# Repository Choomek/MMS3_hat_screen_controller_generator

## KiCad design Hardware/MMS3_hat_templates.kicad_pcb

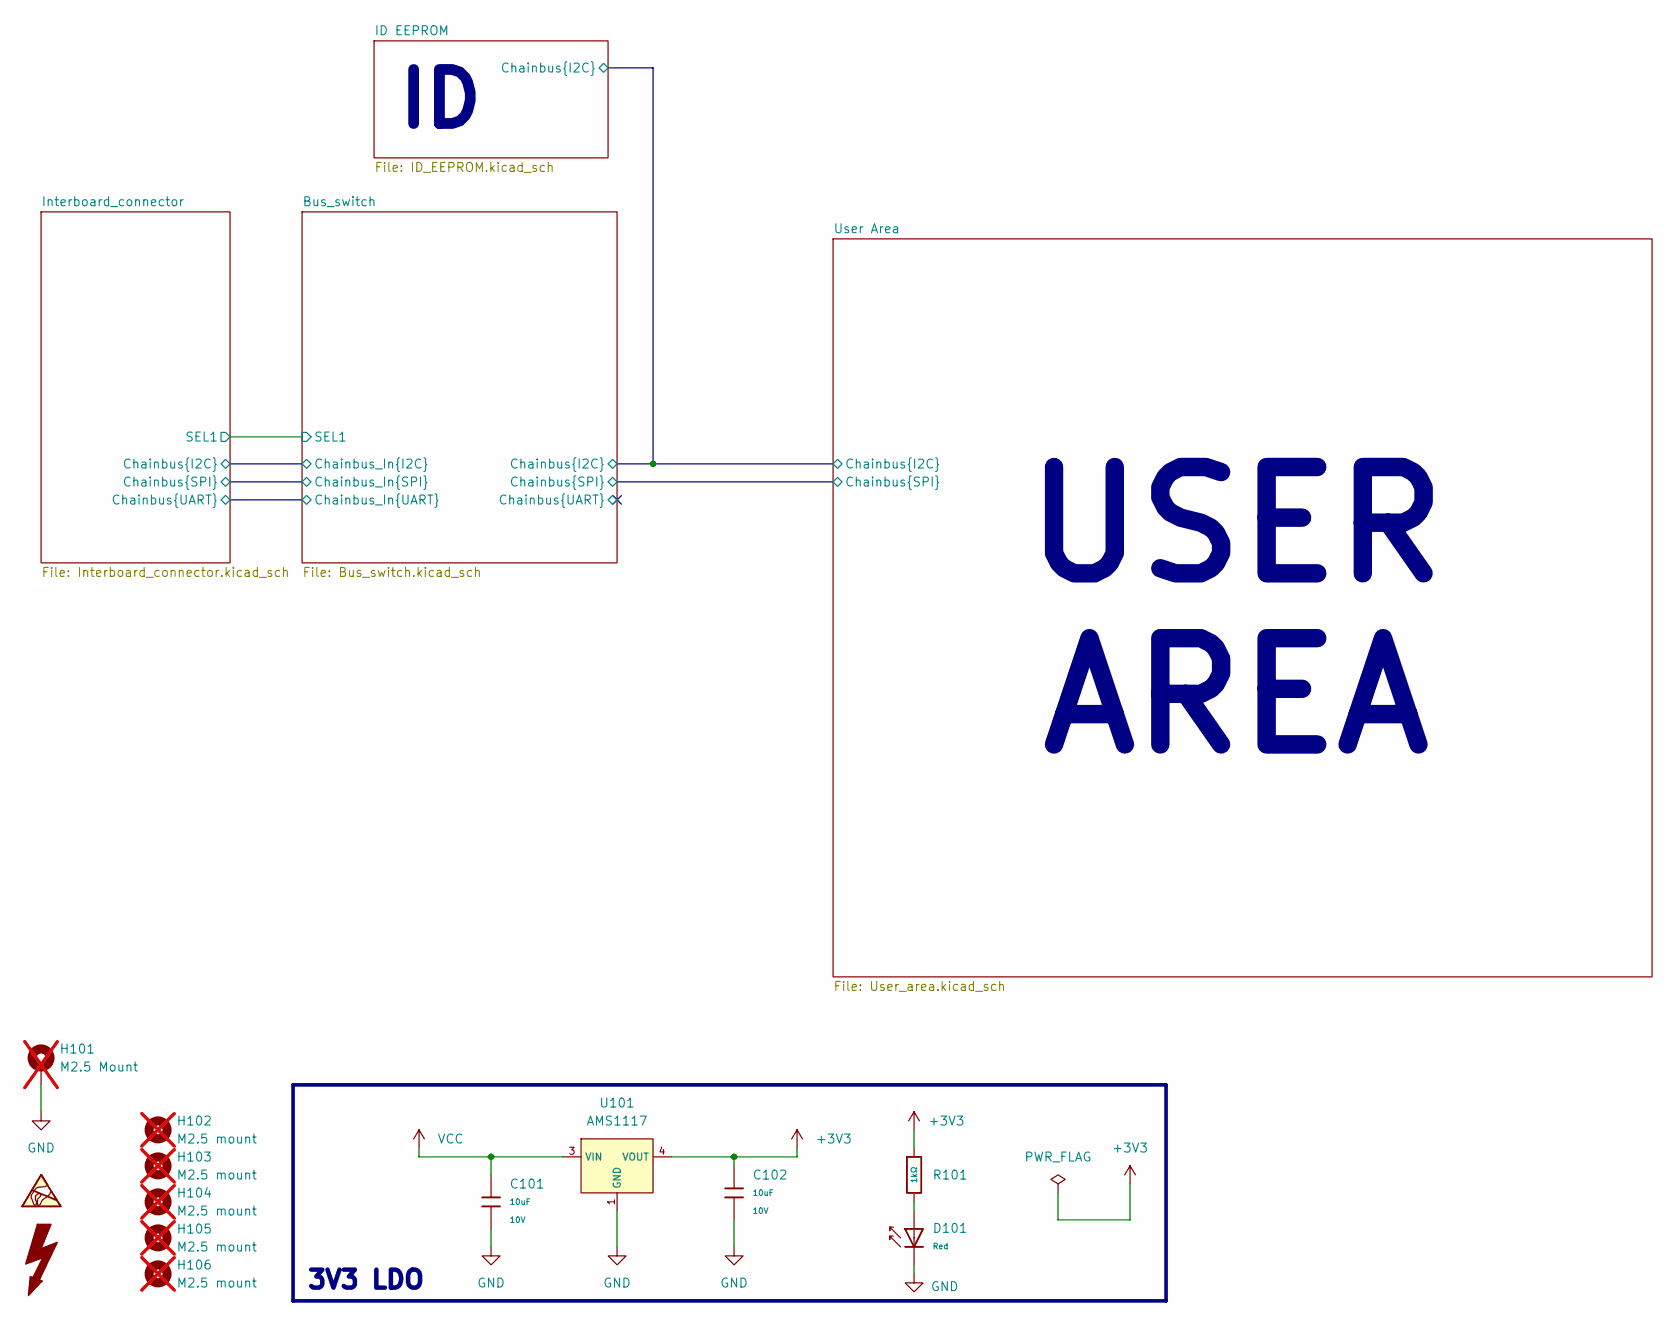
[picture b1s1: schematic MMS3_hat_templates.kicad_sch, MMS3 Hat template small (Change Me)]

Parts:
C101, C102: 10uF; C_0603; Voltage Rated 10V; Tolerance ±10%; Part CL10A106KP8NNNC; LCSC C19702
D101: Red; D_0603; Part KT-0603R; LCSC C2286
H101: M2.5 Mount; MountingHole_2.7mm_M2.5_DIN965_Pad_TopOnly; not fitted
H102, H103, H104, H105, H106: M2.5 mount; MountingHole_2.7mm_M2.5; not fitted
R101: 1kΩ; R_0603; Overload Voltage (Max) 75V; Tolerance ±1%; Part 0603WAF1001T5E; LCSC C21190
U101: AMS1117; SOT-223-3_L6.5-W3.4-P2.30-LS7.0-BR; Output Voltage 3.3V; Dropout Voltage 1.3V@(800mA); Part AMS1117-3.3; LCSC C6186

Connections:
+3V3: C102.1, R101.1, U101.2 (VOUT), U101.4 (VOUT); also elsewhere on the board
GND: C101.2, C102.2, D101.1, H101.1 (1_1), U101.1 (GND); also elsewhere on the board
unnamed: D101.2, R101.2
VCC: C101.1, U101.3 (VIN); also elsewhere on the board

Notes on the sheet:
3V3 LDO
USER AREA

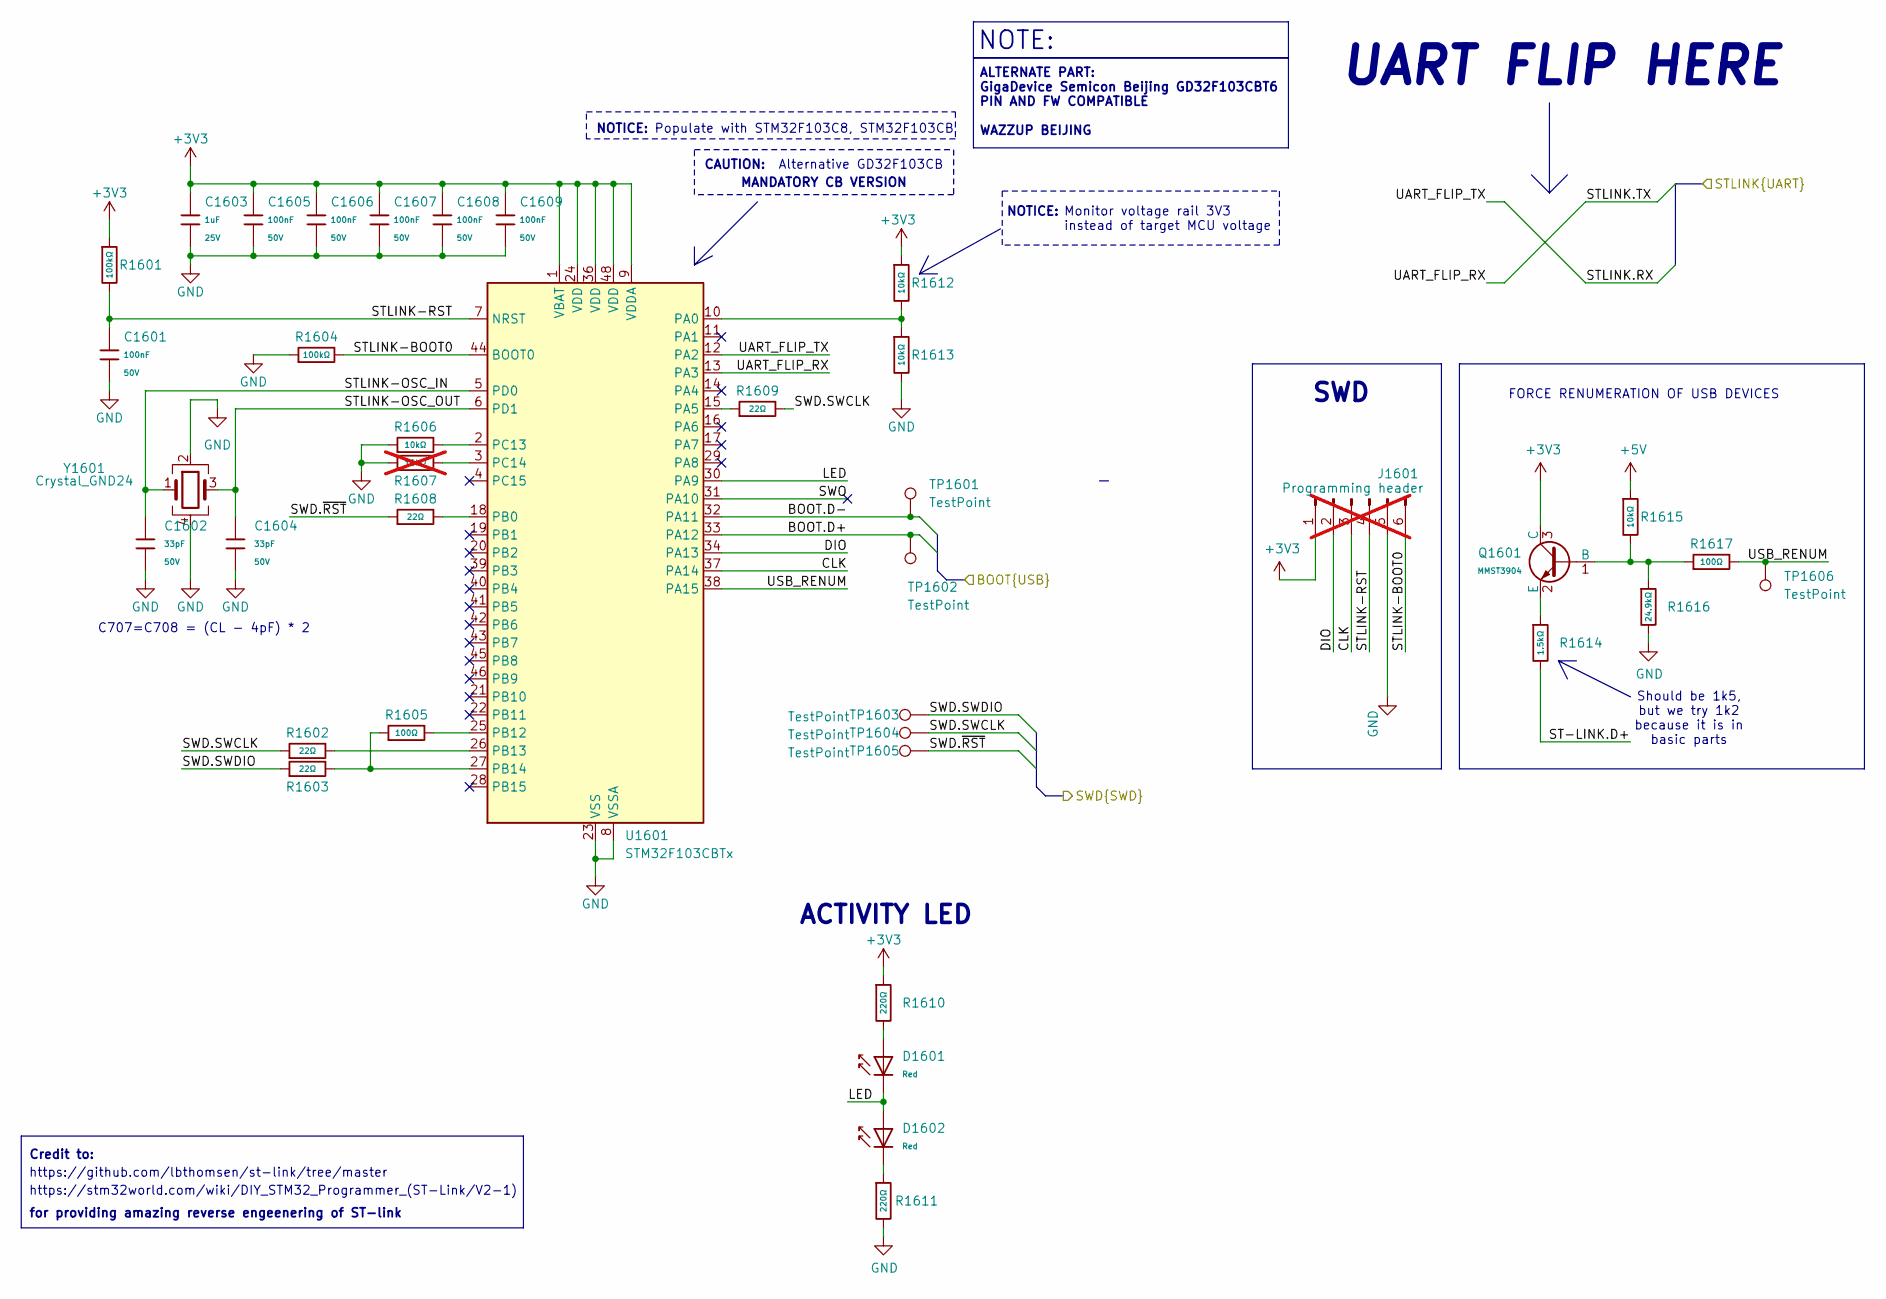
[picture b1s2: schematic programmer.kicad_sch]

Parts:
C1601, C1605, C1606, C1607, C1608, C1609: 100nF; C_0402; Voltage Rated 50V; Tolerance ±10%; Part CL05B104KB54PNC; LCSC C307331
C1602, C1604: 33pF; C_0402; Voltage Rated 50V; Tolerance ±5%; Part 0402CG330J500NT; LCSC C1562
C1603: 1uF; C_0402; Voltage Rated 25V; Tolerance ±10%; Part CL05A105KA5NQNC; LCSC C52923
D1601, D1602: Red; D_0603; Part KT-0603R; LCSC C2286
J1601: Programming header; PinHeader_1x06_P1.27mm_Vertical; not fitted
Q1601: MMST3904; SOT-23; Part MMST3904; LCSC C20526
R1601, R1604: 100kΩ; R_0402; Overload Voltage (Max) 50V; Tolerance ±1%; Part 0402WGF1003TCE; LCSC C25741
R1602, R1603, R1608, R1609: 22Ω; R_0402; Overload Voltage (Max) 50V; Tolerance ±1%; Part 0402WGF220JTCE; LCSC C25092
R1605, R1617: 100Ω; R_0402; Overload Voltage (Max) 50V; Tolerance ±1%; Part 0402WGF1000TCE; LCSC C25076
R1606, R1612, R1613, R1615: 10kΩ; R_0402; Overload Voltage (Max) 50V; Tolerance ±1%; Part 0402WGF1002TCE; LCSC C25744
R1607: 10kΩ; R_0402; Overload Voltage (Max) 50V; Tolerance ±1%; Part 0402WGF1002TCE; LCSC C25744; not fitted
R1610, R1611: 220Ω; R_0402; Overload Voltage (Max) 50V; Tolerance ±1%; Part 0402WGF2200TCE; LCSC C25091
R1614: 1.5kΩ; R_0402; Overload Voltage (Max) 50V; Tolerance ±1%; Part 0402WGF1501TCE; LCSC C25867
R1616: 24.9kΩ; R_0402; Overload Voltage (Max) 50V; Tolerance ±1%; Part 0402WGF2402TCE; LCSC C25874
TP1601, TP1602, TP1603, TP1604, TP1605, TP1606: TestPoint; TestPoint_Pad_D1.0mm
U1601: STM32F103CBTx; LQFP-48_7x7mm_P0.5mm; LCSC C8304
Y1601: Crystal_GND24; CRYSTAL-SMD_4P-L3.2-W2.5-BL; MPN 3225-8.00-20-10-10/4B; LCSC C7424755

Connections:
+3V3: C1603.1, C1605.1, C1606.1, C1607.1, C1608.1, C1609.1, J1601.1, Q1601.3 (C), R1601.1, R1610.1, R1612.1, U1601.1 (VBAT), U1601.9 (VDDA), U1601.24 (VDD), U1601.36 (VDD), U1601.48 (VDD); also elsewhere on the board
+5V: R1615.1; also elsewhere on the board
/User Area/BOOT USB/BOOT.D+: TP1602.1 (1_1), U1601.33 (PA12); also elsewhere on the board
/User Area/BOOT USB/BOOT.D-: TP1601.1 (1_1), U1601.32 (PA11); also elsewhere on the board
/User Area/MCU/PROG_SWD.SWCLK: R1602.1, R1609.2, TP1604.1 (1_1); also elsewhere on the board
/User Area/MCU/PROG_SWD.SWDIO: R1603.1, TP1603.1 (1_1); also elsewhere on the board
/User Area/MCU/PROG_SWD.~RST: R1608.1, TP1605.1 (1_1); also elsewhere on the board
/User Area/programmer/CLK: J1601.3, U1601.37 (PA14)
/User Area/programmer/DIO: J1601.2, U1601.34 (PA13)
/User Area/programmer/LED: D1601.1, D1602.2, U1601.30 (PA9)
/User Area/programmer/ST-LINK.D+: R1614.2
/User Area/programmer/STLINK-BOOT0: J1601.6, R1604.2, U1601.44 (BOOT0)
/User Area/programmer/STLINK-OSC_IN: C1602.1, U1601.5 (PD0), Y1601.1
/User Area/programmer/STLINK-OSC_OUT: C1604.1, U1601.6 (PD1), Y1601.3
/User Area/programmer/STLINK-RST: C1601.1, J1601.4, R1601.2, U1601.7 (NRST)
/User Area/programmer/STLINK.RX: U1601.12 (PA2)
/User Area/programmer/STLINK.TX: U1601.13 (PA3)
/User Area/programmer/SWO: U1601.31 (PA10)
/User Area/programmer/USB_RENUM: R1617.2, TP1606.1 (1_1), U1601.38 (PA15)
GND: C1601.2, C1602.2, C1603.2, C1604.2, C1605.2, C1606.2, C1607.2, C1608.2, C1609.2, J1601.5, R1604.1, R1606.1, R1607.1, R1611.2, R1613.2, R1616.2, U1601.8 (VSSA), U1601.23 (VSS), U1601.35 (VSS), U1601.47 (VSS), Y1601.2, Y1601.4; also elsewhere on the board
unnamed: D1601.2, R1610.2
unnamed: D1602.1, R1611.1
unnamed: Q1601.1 (B), R1615.2, R1616.1, R1617.1
unnamed: Q1601.2 (E), R1614.1
unnamed: R1612.2, R1613.1, U1601.10 (PA0)
unnamed: R1609.1, U1601.15 (PA5)
unnamed: R1608.2, U1601.18 (PB0)
unnamed: R1605.2, U1601.25 (PB12)
unnamed: R1602.2, U1601.26 (PB13)
unnamed: R1603.2, R1605.1, U1601.27 (PB14)
unnamed: R1606.2, U1601.2 (PC13)
unnamed: R1607.2, U1601.3 (PC14)

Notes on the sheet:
Alternative GD32F103CB
Monitor voltage rail 3V3 instead of target MCU voltage
SWD
for providing amazing reverse engeenering of ST-link
MANDATORY CB VERSION
NOTICE:
FORCE RENUMERATION OF USB DEVICES
UART FLIP HERE
C707=C708 = (CL - 4pF) * 2
Should be 1k5, but we try 1k2 because it is in basic parts
https://github.com/lbthomsen/st-link/tree/master
https://stm32world.com/wiki/DIY_STM32_Programmer_(ST-Link/V2-1)
ACTIVITY LED
ALTERNATE PART: GigaDevice Semicon Beijing GD32F103CBT6 PIN AND FW COMPATIBLE WAZZUP BEIJING
Populate with STM32F103C8, STM32F103CB
NOTE:
Credit to:
CAUTION:

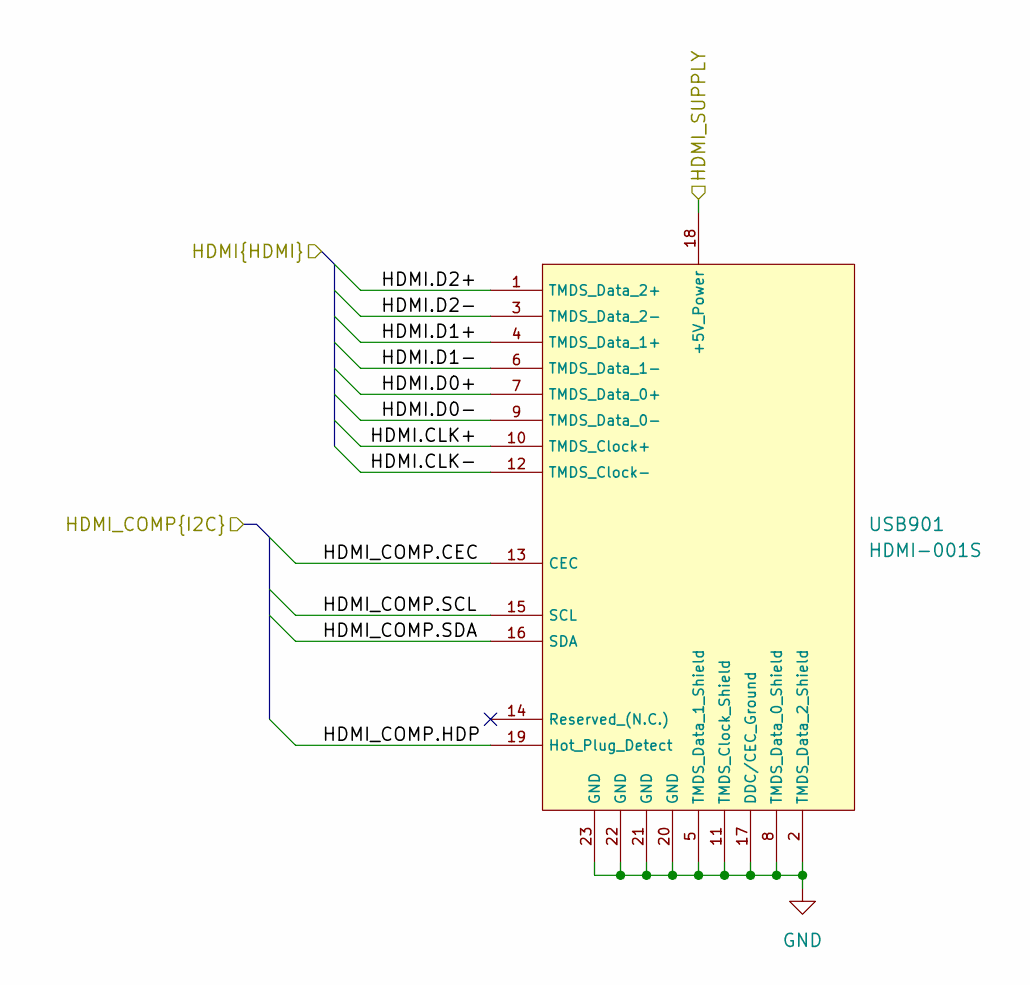
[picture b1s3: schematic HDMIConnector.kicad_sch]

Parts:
USB901: HDMI-001S; C720616_HDMI-SMD_HDMI-001S; LCSC C720616

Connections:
/User Area/HDMI Connector/HDMI.CLK+: USB901.10 (TMDS_Clock+); also elsewhere on the board
/User Area/HDMI Connector/HDMI.CLK-: USB901.12 (TMDS_Clock-); also elsewhere on the board
/User Area/HDMI Connector/HDMI.D0+: USB901.7 (TMDS_Data_0+); also elsewhere on the board
/User Area/HDMI Connector/HDMI.D0-: USB901.9 (TMDS_Data_0-); also elsewhere on the board
/User Area/HDMI Connector/HDMI.D1+: USB901.4 (TMDS_Data_1+); also elsewhere on the board
/User Area/HDMI Connector/HDMI.D1-: USB901.6 (TMDS_Data_1-); also elsewhere on the board
/User Area/HDMI Connector/HDMI.D2+: USB901.1 (TMDS_Data_2+); also elsewhere on the board
/User Area/HDMI Connector/HDMI.D2-: USB901.3 (TMDS_Data_2-); also elsewhere on the board
/User Area/HDMI Connector/HDMI_COMP.CEC: USB901.13 (CEC); also elsewhere on the board
/User Area/HDMI Connector/HDMI_COMP.HDP: USB901.19 (Hot_Plug_Detect); also elsewhere on the board
/User Area/HDMI Connector/HDMI_COMP.SCL: USB901.15 (SCL); also elsewhere on the board
/User Area/HDMI Connector/HDMI_COMP.SDA: USB901.16 (SDA); also elsewhere on the board
/User Area/MCU-HDMI Companion/HDMI_SUPPLY: USB901.18 (+5V_Power); also elsewhere on the board
GND: USB901.2 (TMDS_Data_2_Shield), USB901.5 (TMDS_Data_1_Shield), USB901.8 (TMDS_Data_0_Shield), USB901.11 (TMDS_Clock_Shield), USB901.17 (DDC/CEC_Ground), USB901.20 (GND), USB901.21 (GND), USB901.22 (GND), USB901.23 (GND); also elsewhere on the board

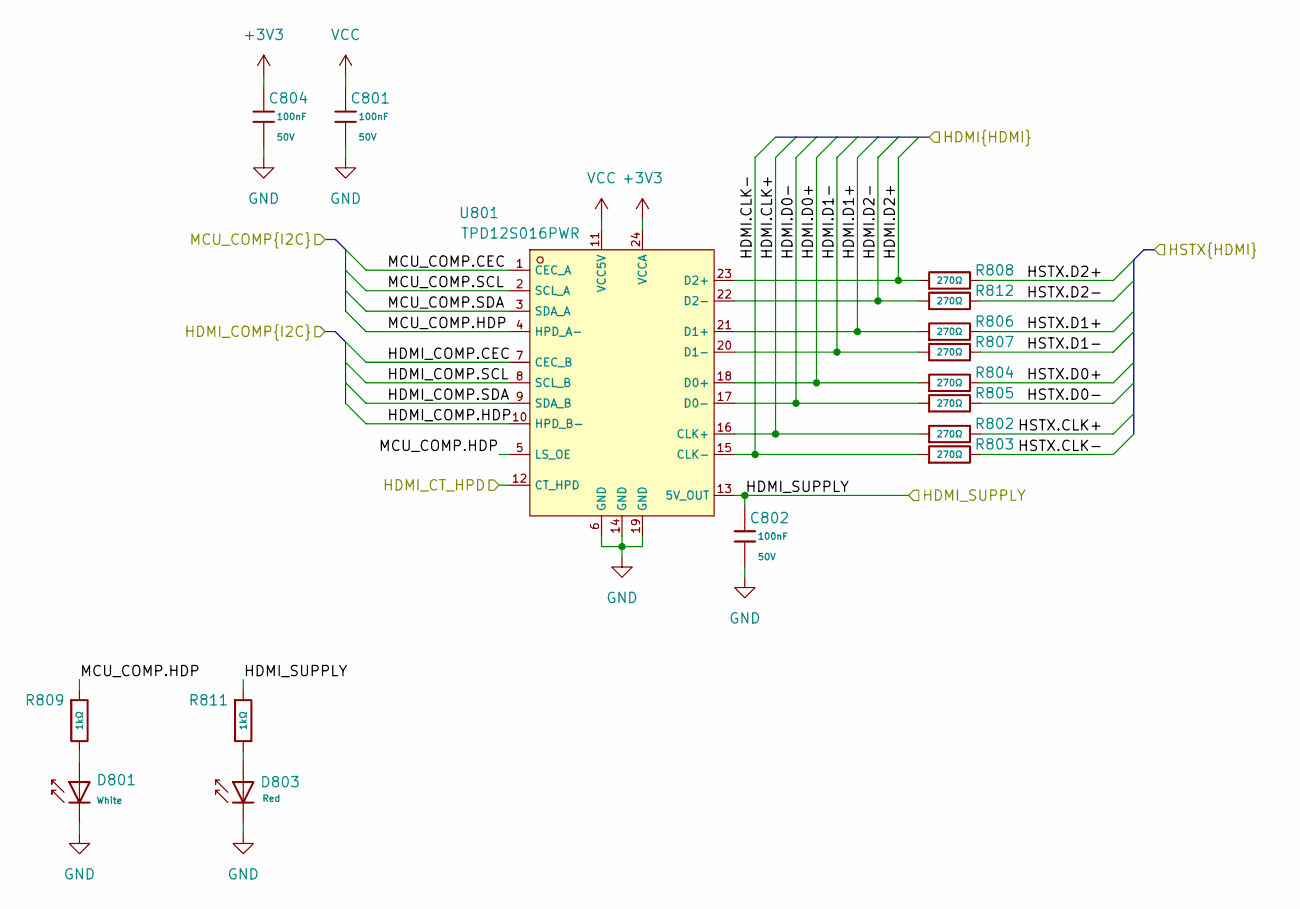
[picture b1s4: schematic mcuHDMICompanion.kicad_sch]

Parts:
C801, C802, C804: 100nF; C_0402; Voltage Rated 50V; Tolerance ±10%; Part CL05B104KB54PNC; LCSC C307331
D801: White; D_0603; Part KT-0603W; LCSC C2290
D803: Red; D_0603; Part KT-0603R; LCSC C2286
R802, R803, R804, R805, R806, R807, R808, R812: 270Ω; R_0603; Overload Voltage (Max) 75V; Tolerance ±1%; Part 0603WAF2700T5E; LCSC C22966
R809, R811: 1kΩ; R_0402; Overload Voltage (Max) 50V; Tolerance ±1%; Part 0402WGF1001TCE; LCSC C11702
U801: TPD12S016PWR; C201665_TSSOP-24_L7_8-W4_4-P0_65-LS6_4-BL; LCSC C201665

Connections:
+3V3: C804.1, U801.24 (VCCA); also elsewhere on the board
/User Area/HDMI Connector/HDMI.CLK+: R802.1, U801.16 (CLK+); also elsewhere on the board
/User Area/HDMI Connector/HDMI.CLK-: R803.1, U801.15 (CLK-); also elsewhere on the board
/User Area/HDMI Connector/HDMI.D0+: R804.1, U801.18 (D0+); also elsewhere on the board
/User Area/HDMI Connector/HDMI.D0-: R805.1, U801.17 (D0-); also elsewhere on the board
/User Area/HDMI Connector/HDMI.D1+: R806.1, U801.21 (D1+); also elsewhere on the board
/User Area/HDMI Connector/HDMI.D1-: R807.1, U801.20 (D1-); also elsewhere on the board
/User Area/HDMI Connector/HDMI.D2+: R808.1, U801.23 (D2+); also elsewhere on the board
/User Area/HDMI Connector/HDMI.D2-: R812.1, U801.22 (D2-); also elsewhere on the board
/User Area/HDMI Connector/HDMI_COMP.CEC: U801.7 (CEC_B); also elsewhere on the board
/User Area/HDMI Connector/HDMI_COMP.HDP: U801.10 (HPD_B-); also elsewhere on the board
/User Area/HDMI Connector/HDMI_COMP.SCL: U801.8 (SCL_B); also elsewhere on the board
/User Area/HDMI Connector/HDMI_COMP.SDA: U801.9 (SDA_B); also elsewhere on the board
/User Area/MCU-HDMI Companion/HDMI_CT_HPD: U801.12 (CT_HPD); also elsewhere on the board
/User Area/MCU-HDMI Companion/HDMI_SUPPLY: C802.1, R811.1, U801.13 (5V_OUT); also elsewhere on the board
/User Area/MCU-HDMI Companion/HSTX.CLK+: R802.2; also elsewhere on the board
/User Area/MCU-HDMI Companion/HSTX.CLK-: R803.2; also elsewhere on the board
/User Area/MCU-HDMI Companion/HSTX.D0+: R804.2; also elsewhere on the board
/User Area/MCU-HDMI Companion/HSTX.D0-: R805.2; also elsewhere on the board
/User Area/MCU-HDMI Companion/HSTX.D1+: R806.2; also elsewhere on the board
/User Area/MCU-HDMI Companion/HSTX.D1-: R807.2; also elsewhere on the board
/User Area/MCU-HDMI Companion/HSTX.D2+: R808.2; also elsewhere on the board
/User Area/MCU-HDMI Companion/HSTX.D2-: R812.2; also elsewhere on the board
/User Area/MCU-HDMI Companion/MCU_COMP.CEC: U801.1 (CEC_A); also elsewhere on the board
/User Area/MCU-HDMI Companion/MCU_COMP.HDP: R809.1, U801.4 (HPD_A-), U801.5 (LS_OE); also elsewhere on the board
/User Area/MCU-HDMI Companion/MCU_COMP.SCL: U801.2 (SCL_A); also elsewhere on the board
/User Area/MCU-HDMI Companion/MCU_COMP.SDA: U801.3 (SDA_A); also elsewhere on the board
GND: C801.2, C802.2, C804.2, D801.1, D803.1, U801.6 (GND), U801.14 (GND), U801.19 (GND); also elsewhere on the board
unnamed: D801.2, R809.2
unnamed: D803.2, R811.2
VCC: C801.1, U801.11 (VCC5V); also elsewhere on the board

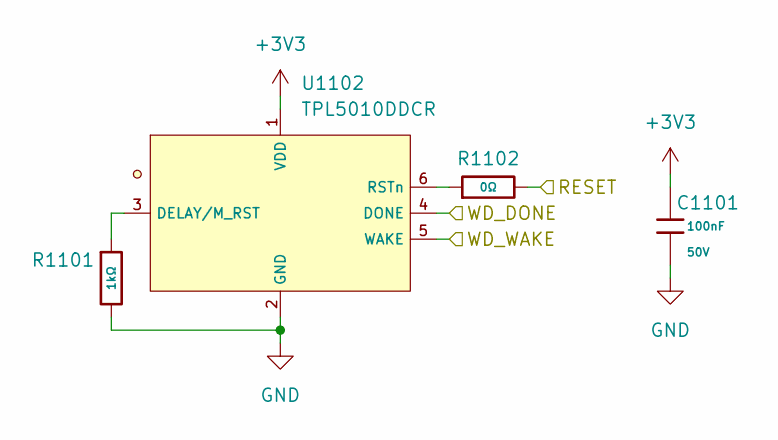
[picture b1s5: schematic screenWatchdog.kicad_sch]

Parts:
C1101: 100nF; C_0402; Voltage Rated 50V; Tolerance ±10%; Part CL05B104KB54PNC; LCSC C307331
R1101: 1kΩ; R_0603; Overload Voltage (Max) 75V; Tolerance ±1%; Part 0603WAF1001T5E; LCSC C21190
R1102: 0Ω; R_0402; Overload Voltage (Max) 50V; Tolerance ±1%; Part 0402WGF0000TCE; LCSC C17168
U1102: TPL5010DDCR; C473912_SOT-23-6_L2_9-W1_6-P0_95-LS2_8-BR; LCSC C473912

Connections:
+3V3: C1101.1, U1102.1 (VDD); also elsewhere on the board
/User Area/MCU/PROG_SWD.~RST: R1102.2; also elsewhere on the board
/User Area/MCU/WD_DONE: U1102.4 (DONE); also elsewhere on the board
/User Area/MCU/WD_WAKE: U1102.5 (WAKE); also elsewhere on the board
GND: C1101.2, R1101.2, U1102.2 (GND); also elsewhere on the board
unnamed: R1101.1, U1102.3 (DELAY/M_RST)
unnamed: R1102.1, U1102.6 (RSTn)

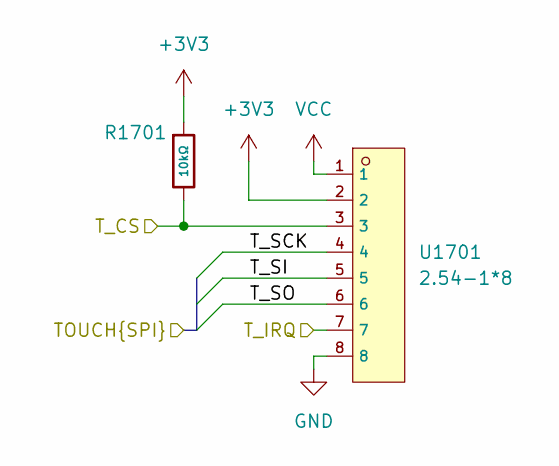
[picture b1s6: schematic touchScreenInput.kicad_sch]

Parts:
R1701: 10kΩ; R_0603; Overload Voltage (Max) 75V; Tolerance ±1%; Part 0603WAF1002T5E; LCSC C25804
U1701: 2.54-1*8; C5156616_HDR-TH_8P-P2_54-V-M; LCSC C5156616

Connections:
+3V3: R1701.1, U1701.2; also elsewhere on the board
/User Area/MCU/T_CS: R1701.2, U1701.3; also elsewhere on the board
/User Area/MCU/T_IRQ: U1701.7; also elsewhere on the board
/User Area/Touch screen input/T_SCK: U1701.4
/User Area/Touch screen input/T_SI: U1701.5
/User Area/Touch screen input/T_SO: U1701.6
GND: U1701.8; also elsewhere on the board
VCC: U1701.1; also elsewhere on the board

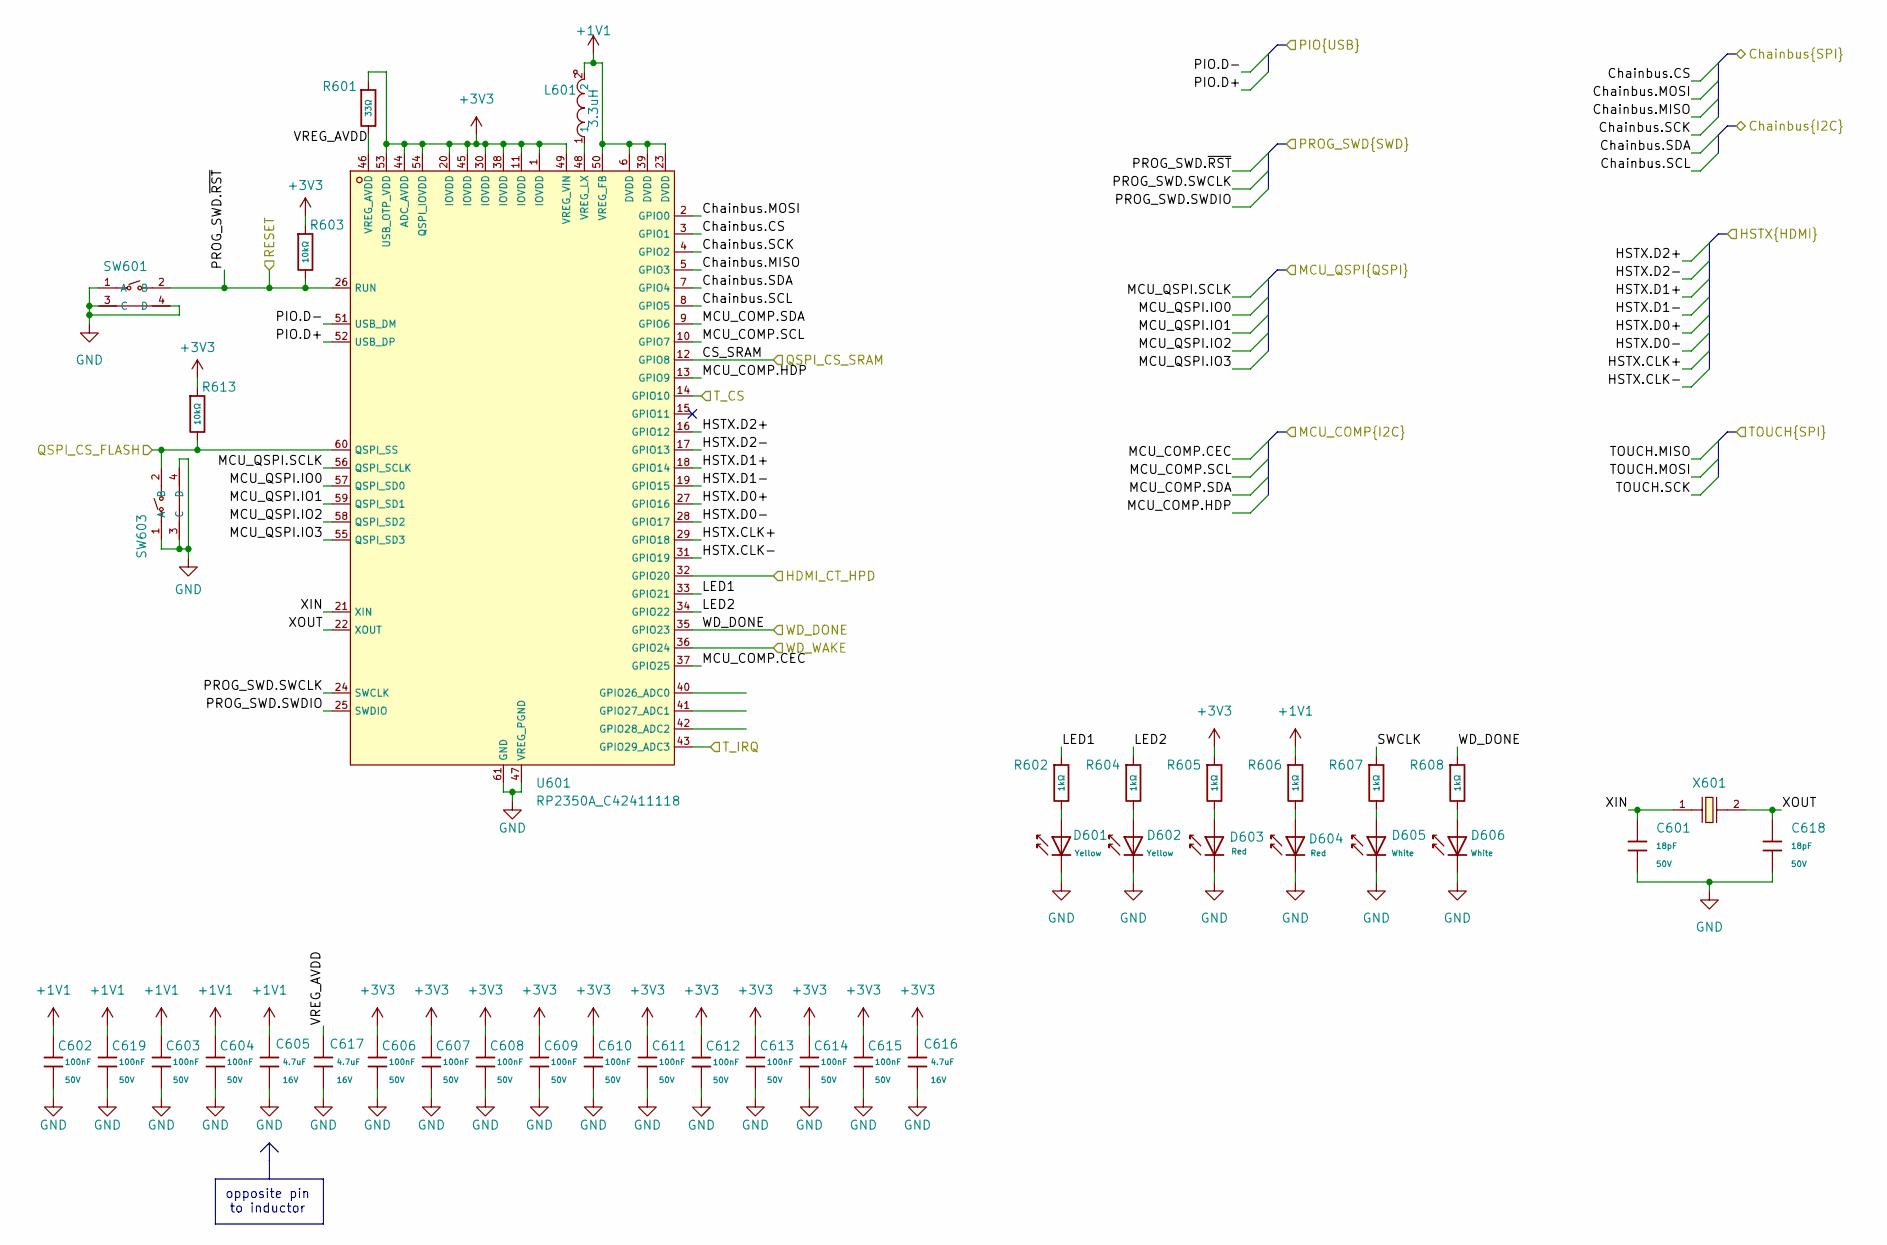
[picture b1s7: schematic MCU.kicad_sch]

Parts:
C601, C618: 18pF; C_0402; Voltage Rated 50V; Tolerance ±5%; Part 0402CG180J500NT; LCSC C1549
C602, C603, C604, C606, C607, C608, C609, C610, C611, C612, C613, C614, C615, C619: 100nF; C_0402; Voltage Rated 50V; Tolerance ±10%; Part CL05B104KB54PNC; LCSC C307331
C605, C616, C617: 4.7uF; C_0603; Voltage Rated 16V; Tolerance ±10%; Part CL10A475KO8NNNC; LCSC C19666
D601, D602: Yellow; D_0603; Forward Voltage (VF) 1.6V~2.6V; Part NCD0603Y2; LCSC C89811
D603, D604: Red; D_0603; Part KT-0603R; LCSC C2286
D605, D606: White; D_0603; Part KT-0603W; LCSC C2290
L601: 3.3uH; C42411119_IND-SMD_L2_0-W1_6_AOTA-B201610S3R3-101-T; LCSC C42411119
R601: 33Ω; R_0603; Overload Voltage (Max) 75V; Tolerance ±1%; Part 0603WAF330JT5E; LCSC C23140
R602, R604, R605, R606, R607, R608: 1kΩ; R_0402; Overload Voltage (Max) 50V; Tolerance ±1%; Part 0402WGF1001TCE; LCSC C11702
R603, R613: 10kΩ; R_0603; Overload Voltage (Max) 75V; Tolerance ±1%; Part 0603WAF1002T5E; LCSC C25804
SW601, SW603: TC-6615Z-12.5-260; C7528758_SW-TH_4P-L7_3-TC-6615Z-12_5-260; LCSC C7528758
U601: RP2350A_C42411118; C42411118_QFN-60_L7_0-W7_0-P0_40-TL-EP3_4; LCSC C42411118
X601: Q13FC1350000400; FC-135R_L3.2-W1.5; Frequency Tolerance ±20ppm; Part Q13FC13500004; LCSC C32346

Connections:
+1V1: C602.1, C603.1, C604.1, C605.1, C619.1, L601.2, R606.1, U601.6 (DVDD), U601.23 (DVDD), U601.39 (DVDD), U601.50 (VREG_FB)
+3V3: C606.1, C607.1, C608.1, C609.1, C610.1, C611.1, C612.1, C613.1, C614.1, C615.1, C616.1, R601.1, R603.1, R605.1, R613.1, U601.1 (IOVDD), U601.11 (IOVDD), U601.20 (IOVDD), U601.30 (IOVDD), U601.38 (IOVDD), U601.44 (ADC_AVDD), U601.45 (IOVDD), U601.49 (VREG_VIN), U601.53 (USB_OTP_VDD), U601.54 (QSPI_IOVDD); also elsewhere on the board
/Bus_switch/Chainbus.CS: U601.3 (GPIO1); also elsewhere on the board
/Bus_switch/Chainbus.MISO: U601.5 (GPIO3); also elsewhere on the board
/Bus_switch/Chainbus.MOSI: U601.2 (GPIO0); also elsewhere on the board
/Bus_switch/Chainbus.SCK: U601.4 (GPIO2); also elsewhere on the board
/Bus_switch/Chainbus.SCL: U601.8 (GPIO5); also elsewhere on the board
/Bus_switch/Chainbus.SDA: U601.7 (GPIO4); also elsewhere on the board
/User Area/FLASH Memory/MCU_QSPI.IO0: U601.57 (QSPI_SD0); also elsewhere on the board
/User Area/FLASH Memory/MCU_QSPI.IO1: U601.59 (QSPI_SD1); also elsewhere on the board
/User Area/FLASH Memory/MCU_QSPI.IO2: U601.58 (QSPI_SD2); also elsewhere on the board
/User Area/FLASH Memory/MCU_QSPI.IO3: U601.55 (QSPI_SD3); also elsewhere on the board
/User Area/FLASH Memory/MCU_QSPI.SCLK: U601.56 (QSPI_SCLK); also elsewhere on the board
/User Area/FLASH Memory/QSPI_CS_FLASH: R613.2, SW603.2 (B), U601.60 (QSPI_SS); also elsewhere on the board
/User Area/HMI USB/PIO.D+: U601.52 (USB_DP); also elsewhere on the board
/User Area/HMI USB/PIO.D-: U601.51 (USB_DM); also elsewhere on the board
/User Area/MCU-HDMI Companion/HDMI_CT_HPD: U601.32 (GPIO20); also elsewhere on the board
/User Area/MCU-HDMI Companion/HSTX.CLK+: U601.29 (GPIO18); also elsewhere on the board
/User Area/MCU-HDMI Companion/HSTX.CLK-: U601.31 (GPIO19); also elsewhere on the board
/User Area/MCU-HDMI Companion/HSTX.D0+: U601.27 (GPIO16); also elsewhere on the board
/User Area/MCU-HDMI Companion/HSTX.D0-: U601.28 (GPIO17); also elsewhere on the board
/User Area/MCU-HDMI Companion/HSTX.D1+: U601.18 (GPIO14); also elsewhere on the board
/User Area/MCU-HDMI Companion/HSTX.D1-: U601.19 (GPIO15); also elsewhere on the board
/User Area/MCU-HDMI Companion/HSTX.D2+: U601.16 (GPIO12); also elsewhere on the board
/User Area/MCU-HDMI Companion/HSTX.D2-: U601.17 (GPIO13); also elsewhere on the board
/User Area/MCU-HDMI Companion/MCU_COMP.CEC: U601.37 (GPIO25); also elsewhere on the board
/User Area/MCU-HDMI Companion/MCU_COMP.HDP: U601.13 (GPIO9); also elsewhere on the board
/User Area/MCU-HDMI Companion/MCU_COMP.SCL: U601.10 (GPIO7); also elsewhere on the board
/User Area/MCU-HDMI Companion/MCU_COMP.SDA: U601.9 (GPIO6); also elsewhere on the board
/User Area/MCU/CS_SRAM: U601.12 (GPIO8); also elsewhere on the board
/User Area/MCU/LED1: R602.1, U601.33 (GPIO21)
/User Area/MCU/LED2: R604.1, U601.34 (GPIO22)
/User Area/MCU/PROG_SWD.SWCLK: U601.24 (SWCLK); also elsewhere on the board
/User Area/MCU/PROG_SWD.SWDIO: U601.25 (SWDIO); also elsewhere on the board
/User Area/MCU/PROG_SWD.~RST: R603.2, SW601.2 (B), U601.26 (RUN); also elsewhere on the board
/User Area/MCU/SWCLK: R607.1
/User Area/MCU/T_CS: U601.14 (GPIO10); also elsewhere on the board
/User Area/MCU/T_IRQ: U601.43 (GPIO29_ADC3); also elsewhere on the board
/User Area/MCU/VREG_AVDD: C617.1, R601.2, U601.46 (VREG_AVDD)
/User Area/MCU/WD_DONE: R608.1, U601.35 (GPIO23); also elsewhere on the board
/User Area/MCU/WD_WAKE: U601.36 (GPIO24); also elsewhere on the board
/User Area/MCU/XIN: C601.1, U601.21 (XIN), X601.1
/User Area/MCU/XOUT: C618.1, U601.22 (XOUT), X601.2
GND: C601.2, C602.2, C603.2, C604.2, C605.2, C606.2, C607.2, C608.2, C609.2, C610.2, C611.2, C612.2, C613.2, C614.2, C615.2, C616.2, C617.2, C618.2, C619.2, D601.1, D602.1, D603.1, D604.1, D605.1, D606.1, SW601.1 (A), SW601.3 (C), SW601.4 (D), SW603.1 (A), SW603.3 (C), SW603.4 (D), U601.47 (VREG_PGND), U601.61 (GND); also elsewhere on the board
unnamed: D601.2, R602.2
unnamed: D602.2, R604.2
unnamed: D603.2, R605.2
unnamed: D604.2, R606.2
unnamed: D605.2, R607.2
unnamed: D606.2, R608.2
unnamed: L601.1, U601.48 (VREG_LX)

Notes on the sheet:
opposite pin to inductor

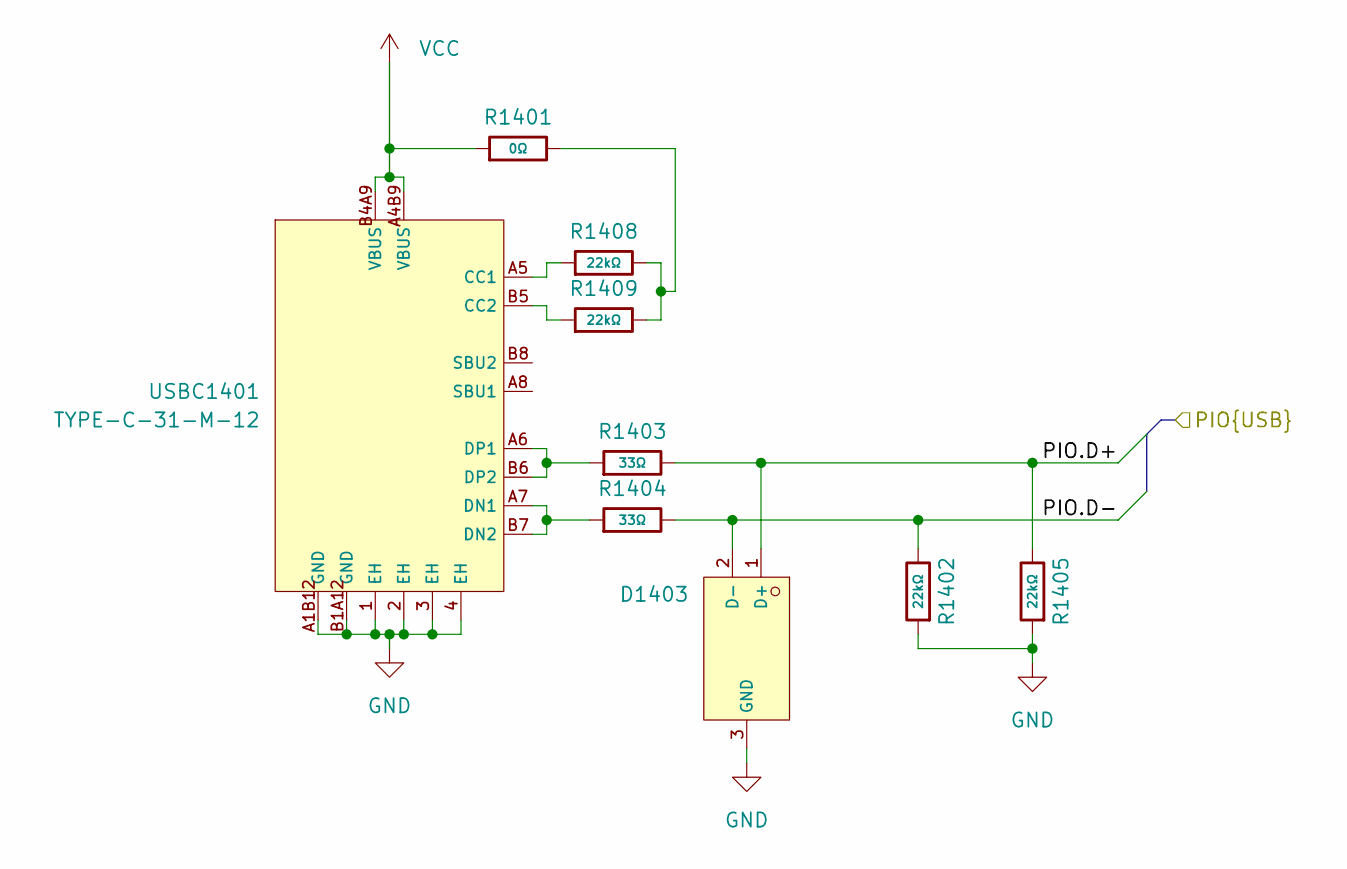
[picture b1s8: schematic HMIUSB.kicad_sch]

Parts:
D1403: TPD2EUSB30DRTR-TP; C2844720_SOT-723-3_L1_2-W0_8-LS1_20-BR; LCSC C2844720
R1401: 0Ω; R_0402; Overload Voltage (Max) 50V; Tolerance ±1%; Part 0402WGF0000TCE; LCSC C17168
R1402, R1405, R1408, R1409: 22kΩ; R_0402; Overload Voltage (Max) 50V; Tolerance ±1%; Part 0402WGF2202TCE; LCSC C25768
R1403, R1404: 33Ω; R_0402; Overload Voltage (Max) 50V; Tolerance ±1%; Part 0402WGF330JTCE; LCSC C25105
USBC1401: TYPE-C-31-M-12; C165948_USB-C_SMD-TYPE-C-31-M-12_1; LCSC C165948

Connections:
/User Area/HMI USB/PIO.D+: D1403.1 (D+), R1403.2, R1405.2; also elsewhere on the board
/User Area/HMI USB/PIO.D-: D1403.2 (D-), R1402.2, R1404.2; also elsewhere on the board
GND: D1403.3 (GND), R1402.1, R1405.1, USBC1401.1 (EH), USBC1401.2 (EH), USBC1401.3 (EH), USBC1401.4 (EH), USBC1401.A1B12 (GND), USBC1401.B1A12 (GND); also elsewhere on the board
unnamed: R1401.2, R1408.2, R1409.2
unnamed: R1408.1, USBC1401.A5 (CC1)
unnamed: R1409.1, USBC1401.B5 (CC2)
unnamed: R1404.1, USBC1401.A7 (DN1), USBC1401.B7 (DN2)
unnamed: R1403.1, USBC1401.A6 (DP1), USBC1401.B6 (DP2)
VCC: R1401.1, USBC1401.A4B9 (VBUS), USBC1401.B4A9 (VBUS); also elsewhere on the board

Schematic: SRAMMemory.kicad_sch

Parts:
C1201: 100nF; C_0402; Voltage Rated 50V; Tolerance ±10%; Part CL05B104KB54PNC; LCSC C307331
R1202: 10kΩ; R_0603; Overload Voltage (Max) 75V; Tolerance ±1%; Part 0603WAF1002T5E; LCSC C25804
U1201: APS6404L-3SQRx-SN; SOIC-8_3.9x4.9mm_P1.27mm

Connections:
+3V3: C1201.1, R1202.1, U1201.8 (VDD); also elsewhere on the board
/User Area/FLASH Memory/MCU_QSPI.IO0: U1201.5 (SI/SIO0); also elsewhere on the board
/User Area/FLASH Memory/MCU_QSPI.IO1: U1201.2 (SO/SIO1); also elsewhere on the board
/User Area/FLASH Memory/MCU_QSPI.IO2: U1201.3 (SIO2); also elsewhere on the board
/User Area/FLASH Memory/MCU_QSPI.IO3: U1201.7 (SIO3); also elsewhere on the board
/User Area/FLASH Memory/MCU_QSPI.SCLK: U1201.6 (SCLK); also elsewhere on the board
/User Area/MCU/CS_SRAM: R1202.2, U1201.1 (~CE); also elsewhere on the board
GND: C1201.2, U1201.4 (VSS); also elsewhere on the board

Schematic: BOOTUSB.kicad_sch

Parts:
D1501: SS510B; D_SMB; Forward Voltage (Vf@If) 0.85V@5.0A; Reverse Voltage (Vr) 100V; Part SS510B; LCSC C7420368
D1504: TPD2EUSB30DRTR-TP; C2844720_SOT-723-3_L1_2-W0_8-LS1_20-BR; LCSC C2844720
R1501, R1502: 33Ω; R_0402; Overload Voltage (Max) 50V; Tolerance ±1%; Part 0402WGF330JTCE; LCSC C25105
R1503, R1505: 5.1kΩ; R_0402; Overload Voltage (Max) 50V; Tolerance ±1%; Part 0402WGF5101TCE; LCSC C25905
USBC1501: TYPE-C-31-M-12; C165948_USB-C_SMD-TYPE-C-31-M-12_1; LCSC C165948

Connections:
/User Area/BOOT USB/BOOT.D+: D1504.1 (D+), R1501.2; also elsewhere on the board
/User Area/BOOT USB/BOOT.D-: D1504.2 (D-), R1502.2; also elsewhere on the board
GND: D1504.3 (GND), R1503.2, R1505.2, USBC1501.1 (EH), USBC1501.2 (EH), USBC1501.3 (EH), USBC1501.4 (EH), USBC1501.A1B12 (GND), USBC1501.B1A12 (GND); also elsewhere on the board
unnamed: D1501.2, USBC1501.A4B9 (VBUS), USBC1501.B4A9 (VBUS)
unnamed: R1505.1, USBC1501.A5 (CC1)
unnamed: R1503.1, USBC1501.B5 (CC2)
unnamed: R1502.1, USBC1501.A7 (DN1), USBC1501.B7 (DN2)
unnamed: R1501.1, USBC1501.A6 (DP1), USBC1501.B6 (DP2)
VCC: D1501.1; also elsewhere on the board
